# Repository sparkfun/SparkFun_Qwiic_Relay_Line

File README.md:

The SparkFun Qwiic Relay Line are a series of Qwiic compatible boards to control high power devices from a microcontroller over I<sup>2</sup>C using the Qwiic interface.

The [SparkFun Qwiic Relay - 1X1A DPDT](https://www.sparkfun.com/sparkfun-qwiic-relay-1x1a-dpdt.html) lets you control high power devices from a microcontroller over I<sup>2</sup>C. This relay breakout uses the G6K-2F-Y DC3 dual-pole/dual-throw relay from Omron Electronic Components capable of switching loads of 1A/30VDC and 0.3A/125VAC (at 40&deg;C) with very low drive currents to switch the relay. This board has one 3-pin screw terminal connector for solderless connection to one of the relay's terminals and a 0.1"-spaced plated through-hole header for connecting the second terminal. It also has options to drive the relay over I<sup>2</sup>C (via Qwiic or a soldered connection) or an external drive input such as a switch or I/O signal. Driving the relay over I<sup>2</sup>C only requires up to 5.8mA@3.3V and driving it from an external input requires up to 33mA@3.3V.

Repository Contents
-------------------

* **/Examples** - Simple Arduino examples for the Qwiic Relay Line 
* **/Hardware** - KiCad design files (.brd, .sch)
* **/docs** - Documentation files for the Qwiic Relay Line

Documentation
--------------
* **[Library](https://github.com/sparkfun/SparkFun_I2C_Expander_Arduino_Library)** - Arduino library for interfacing with 4 and 8-bit I2C GPIO Expanders.
* **[Hookup Guide](https://docs.sparkfun.com/SparkFun_Qwiic_Relay_Line/)** - Basic hookup guide for the Qwiic Relay Line.

Product Versions
----------------
* [COM-30416](https://www.sparkfun.com/sparkfun-qwiic-relay-1x1a-dpdt.html) - Qwiic Relay - 1X1A DPDT

License Information
-------------------

This product is _**open source**_! 

Please review the LICENSE.md file for license information. 

If you have any questions or concerns on licensing, please contact technical support on our [SparkFun forums](https://forum.sparkfun.com/viewforum.php?f=152).

Distributed as-is; no warranty is given.

- Your friends at SparkFun.

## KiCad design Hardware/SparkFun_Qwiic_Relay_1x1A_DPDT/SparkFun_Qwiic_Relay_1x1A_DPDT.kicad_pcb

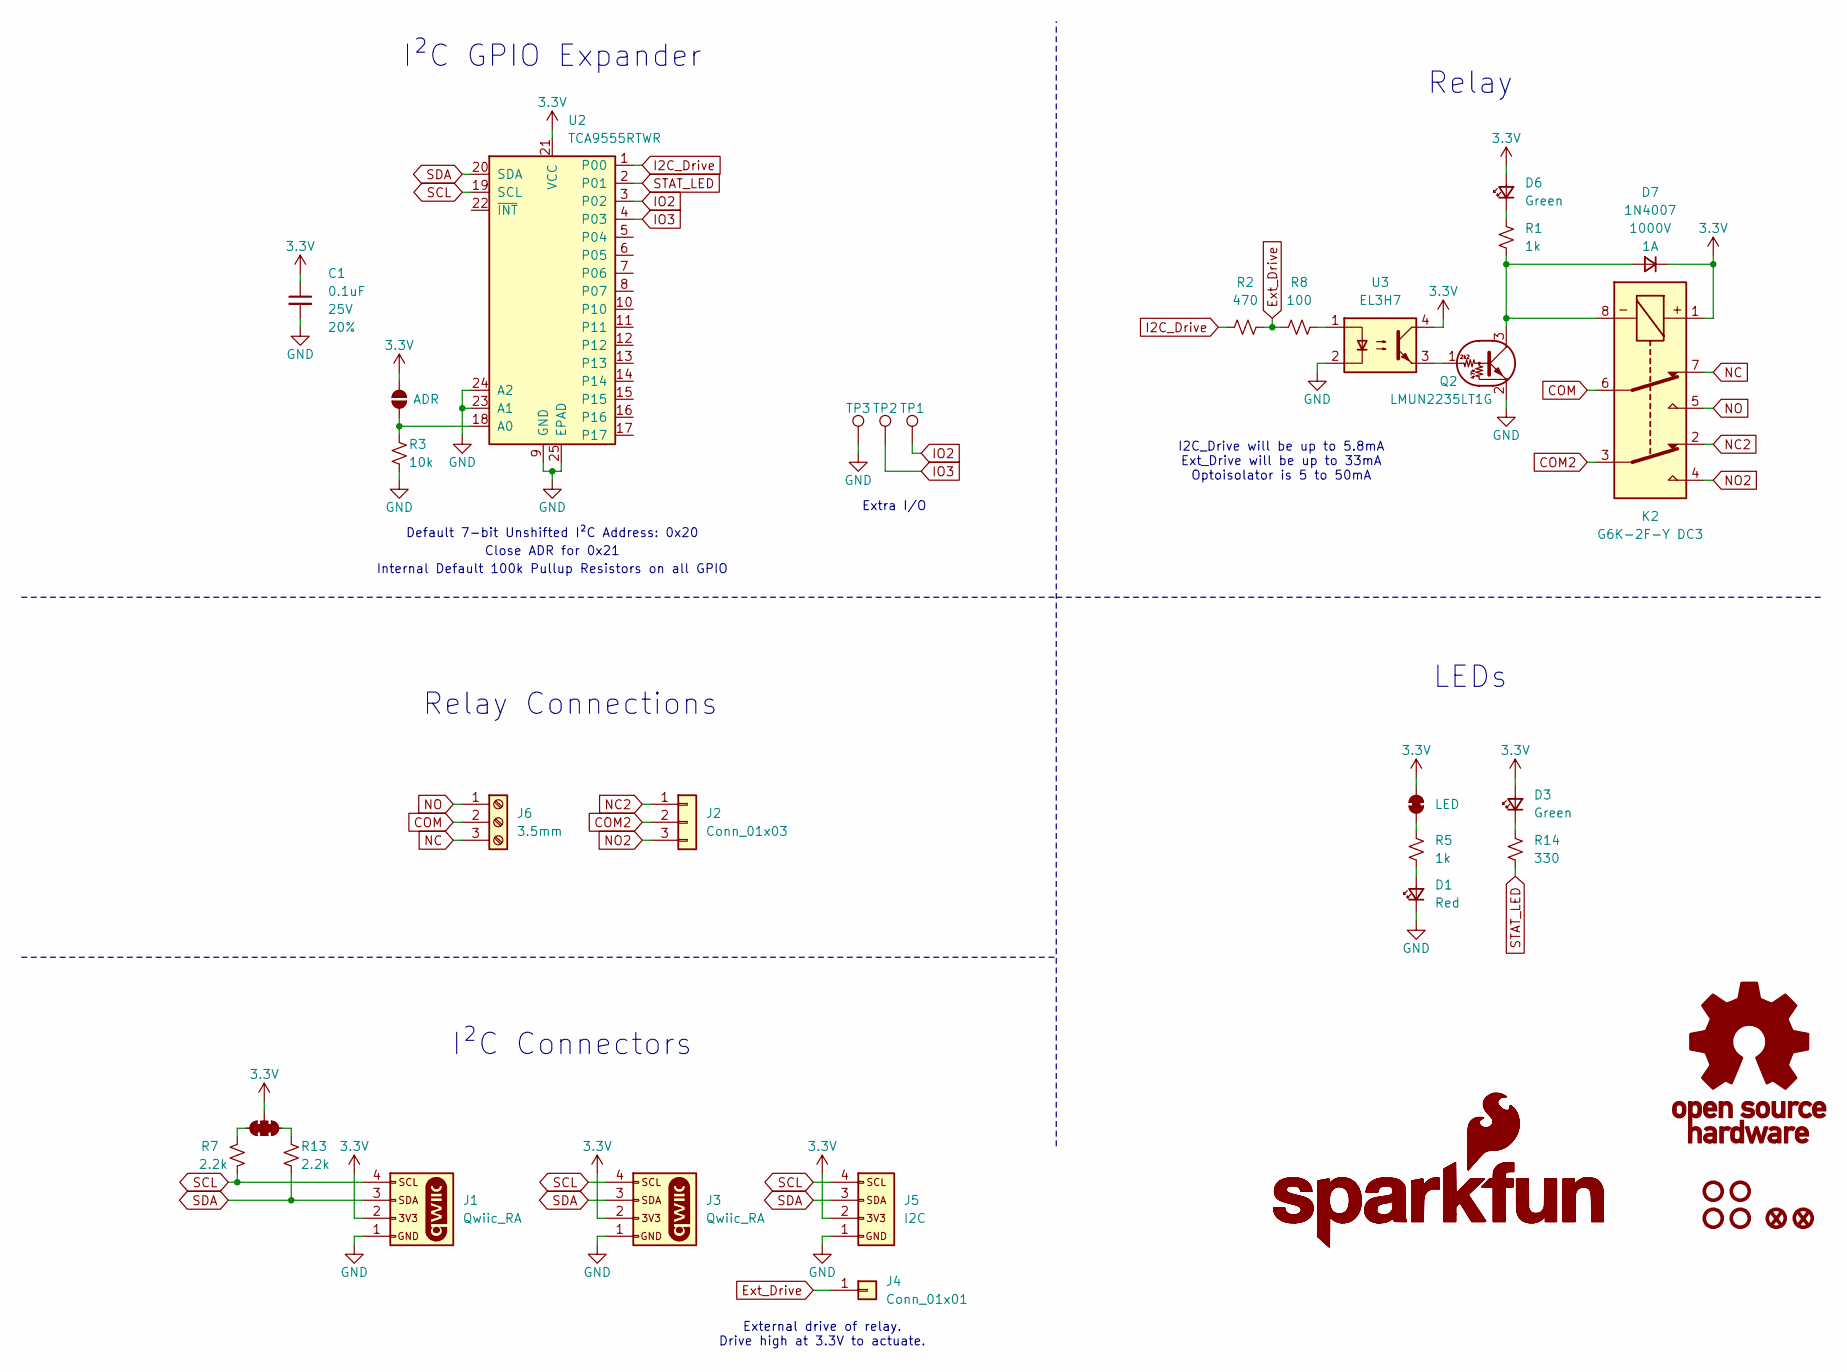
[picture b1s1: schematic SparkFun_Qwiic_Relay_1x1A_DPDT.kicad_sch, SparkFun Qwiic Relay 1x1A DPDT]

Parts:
C1: 0.1uF; C_0603_1608Metric; Voltage 25V; Tolerance 20%
D1: Red; LED_0603_1608Metric_Red
D3, D6: Green; LED_0603_1608Metric_Green
D7: 1N4007; SOD-123
FID3, FID4: Fiducial_0.5mm; Fiducial_0.5mm_Mask1mm
G1: OSHW_Logo; Creative_Commons_License
G3: SparkFun_Logo
G5: SparkFun_Logo; SparkFun_Logo_8mm
J1, J3: Qwiic_RA; JST_1x04_P1.0mm_Horizontal_SMD
J2: Conn_01x03; 1x03_P2.54mm
J4: Conn_01x01; 1x01_P2.54mm
J5: I2C; 1x04_P2.54mm
J6: 3.5mm; ScrewTerminal_1x03_P3.5mm_Horizontal_Black
JP1: ADR; Jumper_2_NO
JP4: LED; Jumper_2_NC_Trace
JP6: Jumper_3_NC-2_Trace
K2: G6K-2F-Y DC3; Relay_DPDT_1A_10.0x6.5mm_SMD
Q2: LMUN2235LT1G; SOT23-3
R1, R5: 1k; R_0603_1608Metric
R2: 470; R_0603_1608Metric
R3: 10k; R_0603_1608Metric
R7, R13: 2.2k; R_0603_1608Metric
R8: 100; R_0603_1608Metric
R14: 330; R_0603_1608Metric
ST1, ST2, ST3, ST4: Standoff
TP1, TP2, TP3: 1.25mm; TestPoint-1.25mm
U2: TCA9555RTWR; QFN-24-1EP_4x4mm_P0.5mm_EP2.45x2.45mm
U3: EL3H7; SSOP-4

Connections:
3.3V: C1.1, D3.2 (A), D6.2 (A), D7.1 (K), J1.2, J3.2, J5.2, JP1.2 (B), JP4.2 (B), JP6.2 (B), K2.1, U2.21 (VCC), U3.4
COM: J6.2, K2.6
COM2: J2.2, K2.3
Ext_Drive: J4.1, R2.2, R8.1
GND: C1.2, D1.1 (K), J1.1, J3.1, J5.1, Q2.2 (E), R3.1, TP3.1, U2.9 (GND), U2.23 (A1), U2.24 (A2), U2.25 (EPAD), U3.2
I2C_Drive: R2.1, U2.1 (P00)
IO2: TP1.1, U2.3 (P02)
IO3: TP2.1, U2.4 (P03)
NC: J6.3, K2.7
NC2: J2.1, K2.2
NO: J6.1, K2.5
NO2: J2.3, K2.4
unnamed: D1.2 (A), R5.1
unnamed: D3.1 (K), R14.1
unnamed: D6.1 (K), R1.2
unnamed: D7.2 (A), K2.8, Q2.3 (C), R1.1
unnamed: JP1.1 (A), R3.2, U2.18 (A0)
unnamed: JP4.1 (A), R5.2
unnamed: JP6.1 (A), R13.2
unnamed: JP6.3 (C), R7.2
unnamed: Q2.1 (B), U3.3
unnamed: R8.2, U3.1
SCL: J1.4, J3.4, J5.4, R7.1, U2.19 (SCL)
SDA: J1.3, J3.3, J5.3, R13.1, U2.20 (SDA)
STAT_LED: R14.2, U2.2 (P01)

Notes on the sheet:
Internal Default 100k Pullup Resistors on all GPIO
Default 7-bit Unshifted I²C Address: 0x20
I²C GPIO Expander
I²C Connectors
External drive of relay. Drive high at 3.3V to actuate.
Extra I/O
LEDs
Relay
Close ADR for 0x21
Relay Connections
I2C_Drive will be up to 5.8mA Ext_Drive will be up to 33mA Optoisolator is 5 to 50mA

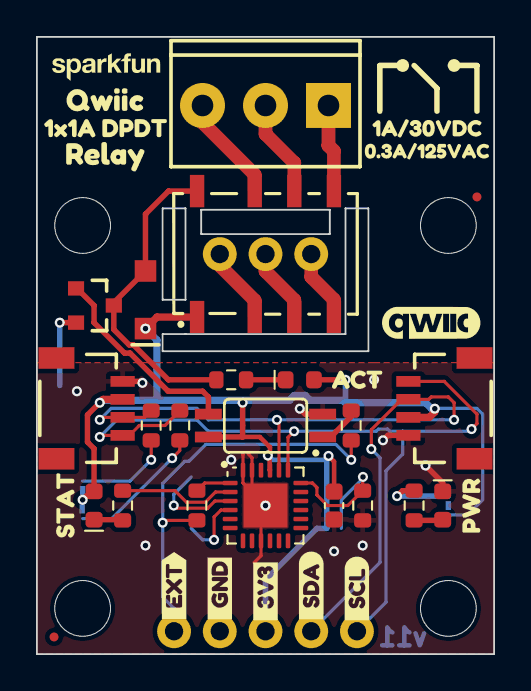
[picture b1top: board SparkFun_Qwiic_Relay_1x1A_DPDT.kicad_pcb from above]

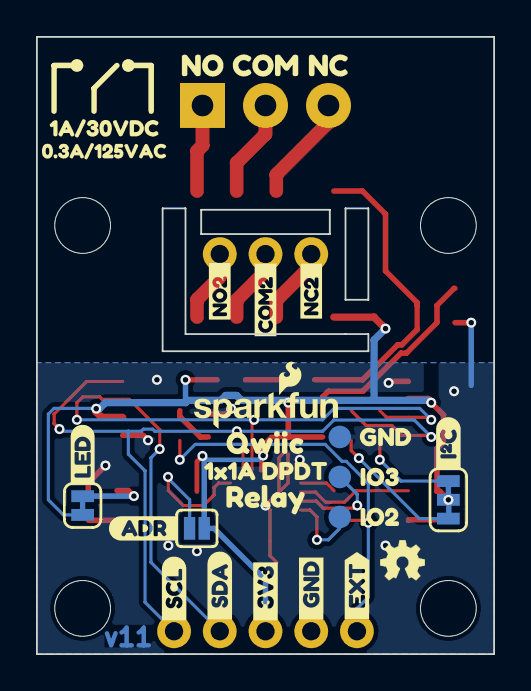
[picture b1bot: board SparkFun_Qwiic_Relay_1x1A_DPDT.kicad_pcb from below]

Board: 2 copper layers, 25.4 x 34.3 mm, 72 parts (30 on the bottom side), 25 nets.

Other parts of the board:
Ref**: Val**; OSHW_Logo_2.5mm
kibuzzard-689A66E2: G***; kibuzzard-689A66E2
kibuzzard-689A66E9: G***; kibuzzard-689A66E9
kibuzzard-689A66EE: G***; kibuzzard-689A66EE
kibuzzard-689A66F4: G***; kibuzzard-689A66F4
kibuzzard-689A642E: G***; kibuzzard-689A642E
kibuzzard-689A6711: G***; kibuzzard-689A6711
kibuzzard-689A6718: G***; kibuzzard-689A6718
kibuzzard-689A6721: G***; kibuzzard-689A6721
kibuzzard-689A6728: G***; kibuzzard-689A6728
kibuzzard-689A6796: G***; kibuzzard-689A6796
kibuzzard-695DDFCB: G***; kibuzzard-695DDFCB
kibuzzard-69310F2E, kibuzzard-69310F2E#2: G***; kibuzzard-69310F2E
kibuzzard-69310F7D: G***; kibuzzard-69310F7D
kibuzzard-69310F28, kibuzzard-69310F28#2: G***; kibuzzard-69310F28
kibuzzard-69310F79: G***; kibuzzard-69310F79
kibuzzard-69310F83: G***; kibuzzard-69310F83
kibuzzard-69339D3B: G***; kibuzzard-69339D3B
kibuzzard-69339D34: G***; kibuzzard-69339D34
kibuzzard-693110A5: G***; kibuzzard-693110A5
kibuzzard-693110C2: G***; kibuzzard-693110C2
kibuzzard-693110C5: G***; kibuzzard-693110C5
kibuzzard-693716BB: G***; kibuzzard-693716BB
kibuzzard-693716F7: G***; kibuzzard-693716F7
kibuzzard-693717B6: G***; kibuzzard-693717B6
kibuzzard-6931071F: G***; kibuzzard-6931071F
kibuzzard-6937168C, kibuzzard-6937168C#2: G***; kibuzzard-6937168C
kibuzzard-69311012: G***; kibuzzard-69311012
kibuzzard-69325721: G***; kibuzzard-69325721
kibuzzard-69371669, kibuzzard-69371669#2: G***; kibuzzard-69371669
kibuzzard-69371817: G***; kibuzzard-69371817
kibuzzard-69371825: G***; kibuzzard-69371825

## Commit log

2025-12-08 Add 1x1A DPDT
2026-01-07 Post review update
2026-01-08 Adds prod-id to 16-bit IO Expander
2026-02-13 Fix polarized relay. Increase version on PCB and SCH.
2026-03-02 Add product link
2026-03-18 Initial docs commit
    Adding all documentation content files and GH pages build files. Prep for initial review.
2026-03-19 Docs review update
    Documentation final review changes. Adding GH pages build file.
2026-03-19 Link fixes
    Should fix build errors related to bad links.
2026-03-19 Create README.md
    Adding README to main repo page.

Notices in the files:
parts and their libraries:
https://creativecommons.org/licenses/by-sa/4.0
Released under the Creative Commons Attribution Share-Alike 4.0 License
